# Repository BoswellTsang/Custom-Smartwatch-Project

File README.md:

# Custom Smartwatch — Electronics and PCB Development

**Status:** In progress (November 2026) · **Project:** Independent hardware design  
**Focus:** KiCad · low-power electronics · BLE/RF · power management · sensors · mixed-signal layout

> Designing a custom smartwatch at the integrated-circuit and PCB level. The intended platform combines a Nordic nRF54L15 MCU, 250 mAh LiPo battery, charger/fuel gauge, 3.0 V and 1.8 V power rails, graphical display, IMU, ambient light sensor and a separate optical heart-rate PCB.

<!-- Add an image of the real schematic or PCB here once available. -->

## Project status

This is **not a completed smartwatch**. Major components have been selected, custom schematic symbols and supporting circuits are in development, and the separate heart-rate AFE board has reached preliminary fine-pitch routing. Fabrication, firmware bring-up and measured performance are still future work.

| Subsystem | Selected hardware / design |
| --- | --- |
| Microcontroller | Nordic nRF54L15, QFN48, Bluetooth Low Energy |
| Battery | MIKROE-4471 / MLP502030, protected 250 mAh, 3.7 V LiPo |
| Charger | TI BQ25185DLHR with power-path management |
| Main regulator | TI TPS63900DSKR buck-boost; target 3.0 V |
| Secondary regulator | TI TPS7A2018PDBVR LDO; target 1.8 V |
| Fuel gauge | MAX17048G+T10 |
| Battery temperature monitor | 10 kΩ NTC |
| IMU | Bosch BMI270, 3-axis accelerometer + gyroscope |
| Ambient light | TI OPT3004, I²C |
| RF antenna | Johanson 2450AT18A0100001E, 2.45 GHz chip antenna |
| Display | RONBO RB0128Y2447A-GF70; FPC interface being checked |
| Optical sensing | MAX86141ENP+T AFE on a separate proposed PCB |
| Board plan | Main smartwatch board + optical sensor daughterboard |

## Functional architecture (prototype)

## Work completed so far

### Power architecture and schematic
- Selected the BQ25185, TPS63900, TPS7A20, MAX17048 and protected LiPo battery.
- Defined target **3.0 V and 1.8 V** supplies and investigated shutdown/enable control.
- Researched **2.2 µH** buck-boost inductor, **10 µF** input and **22 µF** output capacitors and supporting resistor options from datasheets.
- Evaluated 0402/0603 passives, voltage ratings, tolerances and assembly feasibility.
- Created and verified custom KiCad symbols for several ICs and sensors.

### MCU, RF and digital peripherals
- Investigated nRF54L15 QFN48 pin mapping, GPIO, SPI/I²C and power requirements.
- Selected a 2.45 GHz chip antenna and drafted a matching network; RF layout and measurement remain future work.
- Investigated **BMI270** interface options (I²C, 3-/4-wire SPI) and **OPT3004** I²C pull-ups (10 kΩ versus 2.2 kΩ).
- Examined FPC connector selection, display supply pins and LED backlight components including a **10 µH** inductor and **1 µF** capacitors.

### Optical sensing PCB
- Selected a **MAX86141**, a 20-ball **0.4 mm-pitch** WLP optical AFE.
- Began routing its supply, ground and sensitive photodiode input nets.
- Investigated a **4-layer** layout, PD_GND shielding and fine-pitch signal escapes.
- Identified unresolved AFE interrupt routing and LED-supply compatibility.

## Roadmap

- [x] Establish preliminary system architecture and select major ICs
- [x] Start custom schematic symbols and power circuits
- [x] Investigate antenna network, display and sensor interfaces
- [x] Start optical AFE board routing
- [x] Finish schematic review, pin mapping and ERC
- [ ] Complete main PCB and optical AFE PCB layout / DRC
- [ ] Fabricate and assemble the first prototypes
- [ ] Bring up power, MCU, sensors, display and BLE
- [ ] Record active/sleep current and battery runtime
- [ ] Validate optical measurement and RF performance

## Engineering documentation

- [Architecture and power domains](docs/architecture.md)
- [Component selection and design decisions](docs/design-decisions.md)
- [Bring-up and validation plan](docs/testing.md)
- [Progress log](docs/progress-log.md)
- [Hardware source file guide](hardware/README.md)
- [Firmware development status](firmware/README.md)

Native KiCad, fabrication, firmware and actual project images will be added as they become available. No unmeasured performance is asserted.

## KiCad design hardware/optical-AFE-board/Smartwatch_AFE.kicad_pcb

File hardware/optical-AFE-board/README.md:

# Custom Smartwatch - Optical AFE PCB Board

**Status** In Progress

# Overview
This is a separate PCB board housing the optical AFE components needed for heart rate sensing. This board will connect to the main board through a surface mounted connector.

The entire board is 8.4 mm in radius.

# Component Selection:

| Subsystem | Selected hardware / design |
| --- | --- |
| Secondary regulator | TI TPS7A2018PDBVR LDO; target 1.8 V |
| Ambient light | TI OPT3004, I²C |
| Optical sensing | MAX86141ENP+T AFE |

# Schematic (Prototype)

# PCB Layout

**Combined Layers**

**Front Copper (F.Cu) Layer**

**Back Copper (B.Cu) Layer**

**3-D Render**

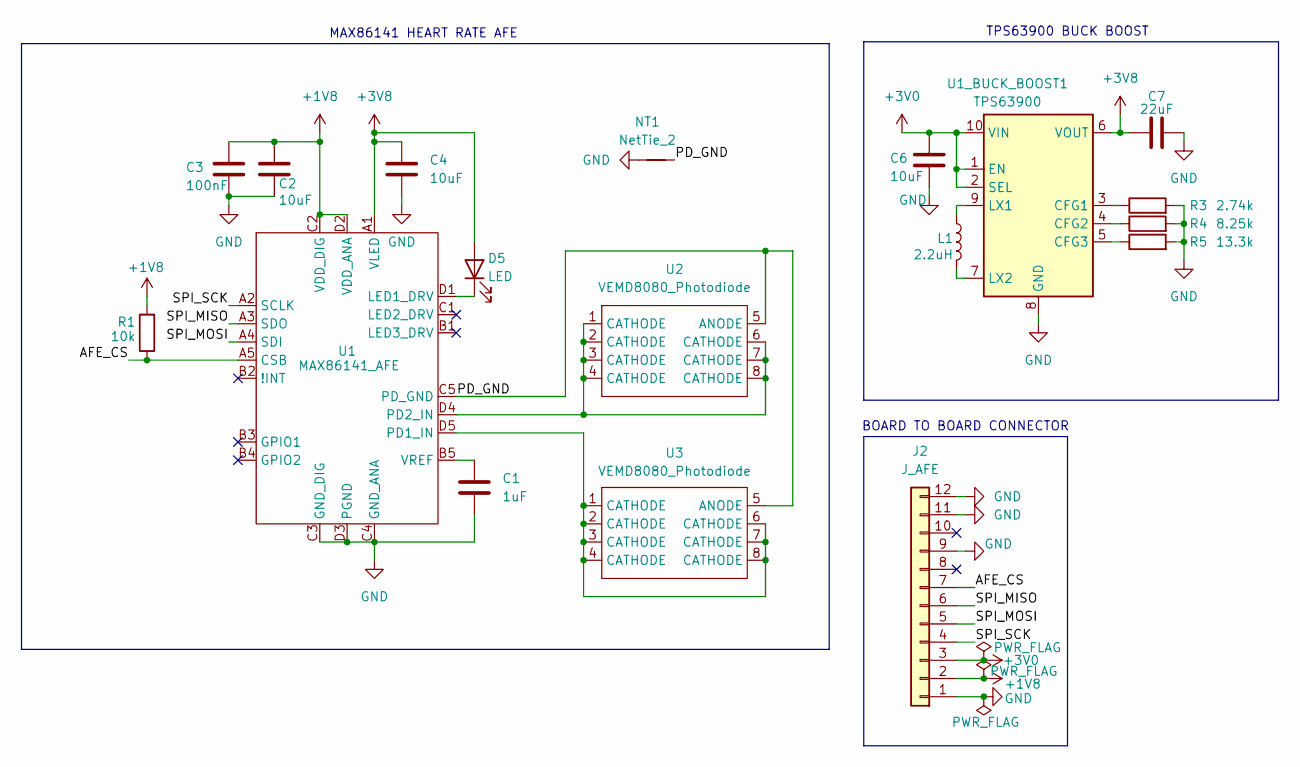
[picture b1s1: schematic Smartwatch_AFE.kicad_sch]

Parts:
C1: 1uF; C_0402_1005Metric_Pad0.74x0.62mm_HandSolder; MPN CC0402MRX5R6BB105
C2, C4: 10uF; C_0603_1608Metric_Pad1.08x0.95mm_HandSolder; MPN GRM188R61A106KE69D
C3: 100nF; C_0402_1005Metric_Pad0.74x0.62mm_HandSolder; MPN GRM155R71C104KA88D
C6: 10uF; C_0603_1608Metric_Pad1.08x0.95mm_HandSolder; MPN GRM188R60J106ME47
C7: 22uF; C_0603_1608Metric_Pad1.08x0.95mm_HandSolder; MPN GRM187R60J226ME15
D5: LED; OSRAM_LT_PWSG_TopMount; MPN LT PWSG-BACA-36-N626-20-SF
J2: J_AFE; Hirose_DF40C-12DP-0.4V_2x06-1MP_P0.4mm; MPN DF40C-12DP-0.4V(51)
L1: 2.2uH; L_1008_2520Metric_Pad1.43x2.20mm_HandSolder; MPN DFE252010F-2R2M
NT1: NetTie_2; NetTie-2_SMD_Pad0.5mm
R1: 10k; R_0402_1005Metric_Pad0.72x0.64mm_HandSolder; MPN RC0402FR-0710KL
R3: 2.74k; R_0603_1608Metric_Pad0.98x0.95mm_HandSolder; MPN RC0603FR-072K74L
R4: 8.25k; R_0603_1608Metric_Pad0.98x0.95mm_HandSolder; MPN RC0603FR-078K25L
R5: 13.3k; R_0603_1608Metric_Pad0.98x0.95mm_HandSolder; MPN RC0603FR-0713K3L
U1: MAX86141_AFE; MAX86141; MPN MAX86141ENP+T
U1_BUCK_BOOST1: TPS63900; WSON-10-1EP_2.5x2.5mm_P0.5mm_EP1.2x2mm_ThermalVias; MPN TPS63900DSKR
U2, U3: VEMD8080_Photodiode; VEMD8080; MPN VEMD8080

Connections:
+1V8: C2.1, C3.1, J2.2, R1.2, U1.C2 (VDD_DIG), U1.D2 (VDD_ANA)
+3V0: C6.1, J2.3, U1_BUCK_BOOST1.1 (EN), U1_BUCK_BOOST1.2 (SEL), U1_BUCK_BOOST1.10 (VIN)
+3V8: C4.1, C7.1, D5.2 (A), U1.A1 (VLED), U1_BUCK_BOOST1.6 (VOUT)
/AFE_CS: J2.7, R1.1, U1.A5 (CSB)
/PD_GND: NT1.2, U1.C5 (PD_GND), U2.5 (ANODE), U3.5 (ANODE)
/SPI_MISO: J2.6, U1.A3 (SDO)
/SPI_MOSI: J2.5, U1.A4 (SDI)
/SPI_SCK: J2.4, U1.A2 (SCLK)
GND: C1.2, C2.2, C3.2, C4.2, C6.2, C7.2, J2.1, J2.9, J2.11, J2.12, NT1.1, R3.2, R4.2, R5.2, U1.C3 (GND_DIG), U1.C4 (GND_ANA), U1.D3 (PGND), U1_BUCK_BOOST1.8 (GND), U1_BUCK_BOOST1.11 (GND)
unnamed: D5.1 (K), U1.D1 (LED1_DRV)
unnamed: U1.D5 (PD1_IN), U3.1 (CATHODE), U3.2 (CATHODE), U3.3 (CATHODE), U3.4 (CATHODE), U3.6 (CATHODE), U3.7 (CATHODE), U3.8 (CATHODE)
unnamed: U1.D4 (PD2_IN), U2.1 (CATHODE), U2.2 (CATHODE), U2.3 (CATHODE), U2.4 (CATHODE), U2.6 (CATHODE), U2.7 (CATHODE), U2.8 (CATHODE)
unnamed: C1.1, U1.B5 (VREF)
unnamed: R3.1, U1_BUCK_BOOST1.3 (CFG1)
unnamed: R4.1, U1_BUCK_BOOST1.4 (CFG2)
unnamed: R5.1, U1_BUCK_BOOST1.5 (CFG3)
unnamed: L1.1, U1_BUCK_BOOST1.9 (LX1)
unnamed: L1.2, U1_BUCK_BOOST1.7 (LX2)

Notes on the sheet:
BOARD TO BOARD CONNECTOR
MAX86141 HEART RATE AFE
TPS63900 BUCK BOOST

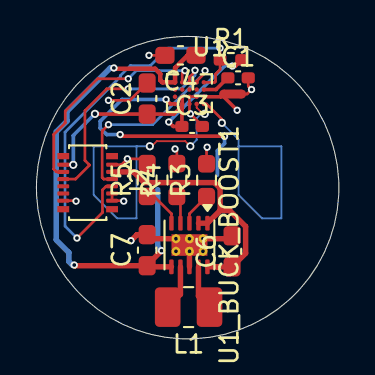
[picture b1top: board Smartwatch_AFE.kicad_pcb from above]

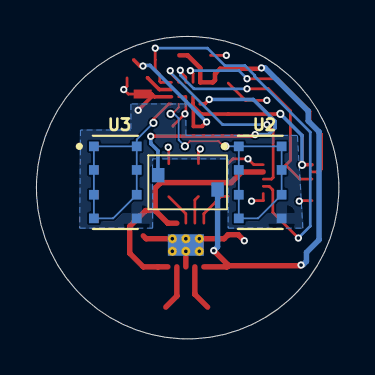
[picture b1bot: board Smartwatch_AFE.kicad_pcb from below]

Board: 4 copper layers, 16.8 x 16.8 mm, 18 parts (3 on the bottom side), 18 nets.
